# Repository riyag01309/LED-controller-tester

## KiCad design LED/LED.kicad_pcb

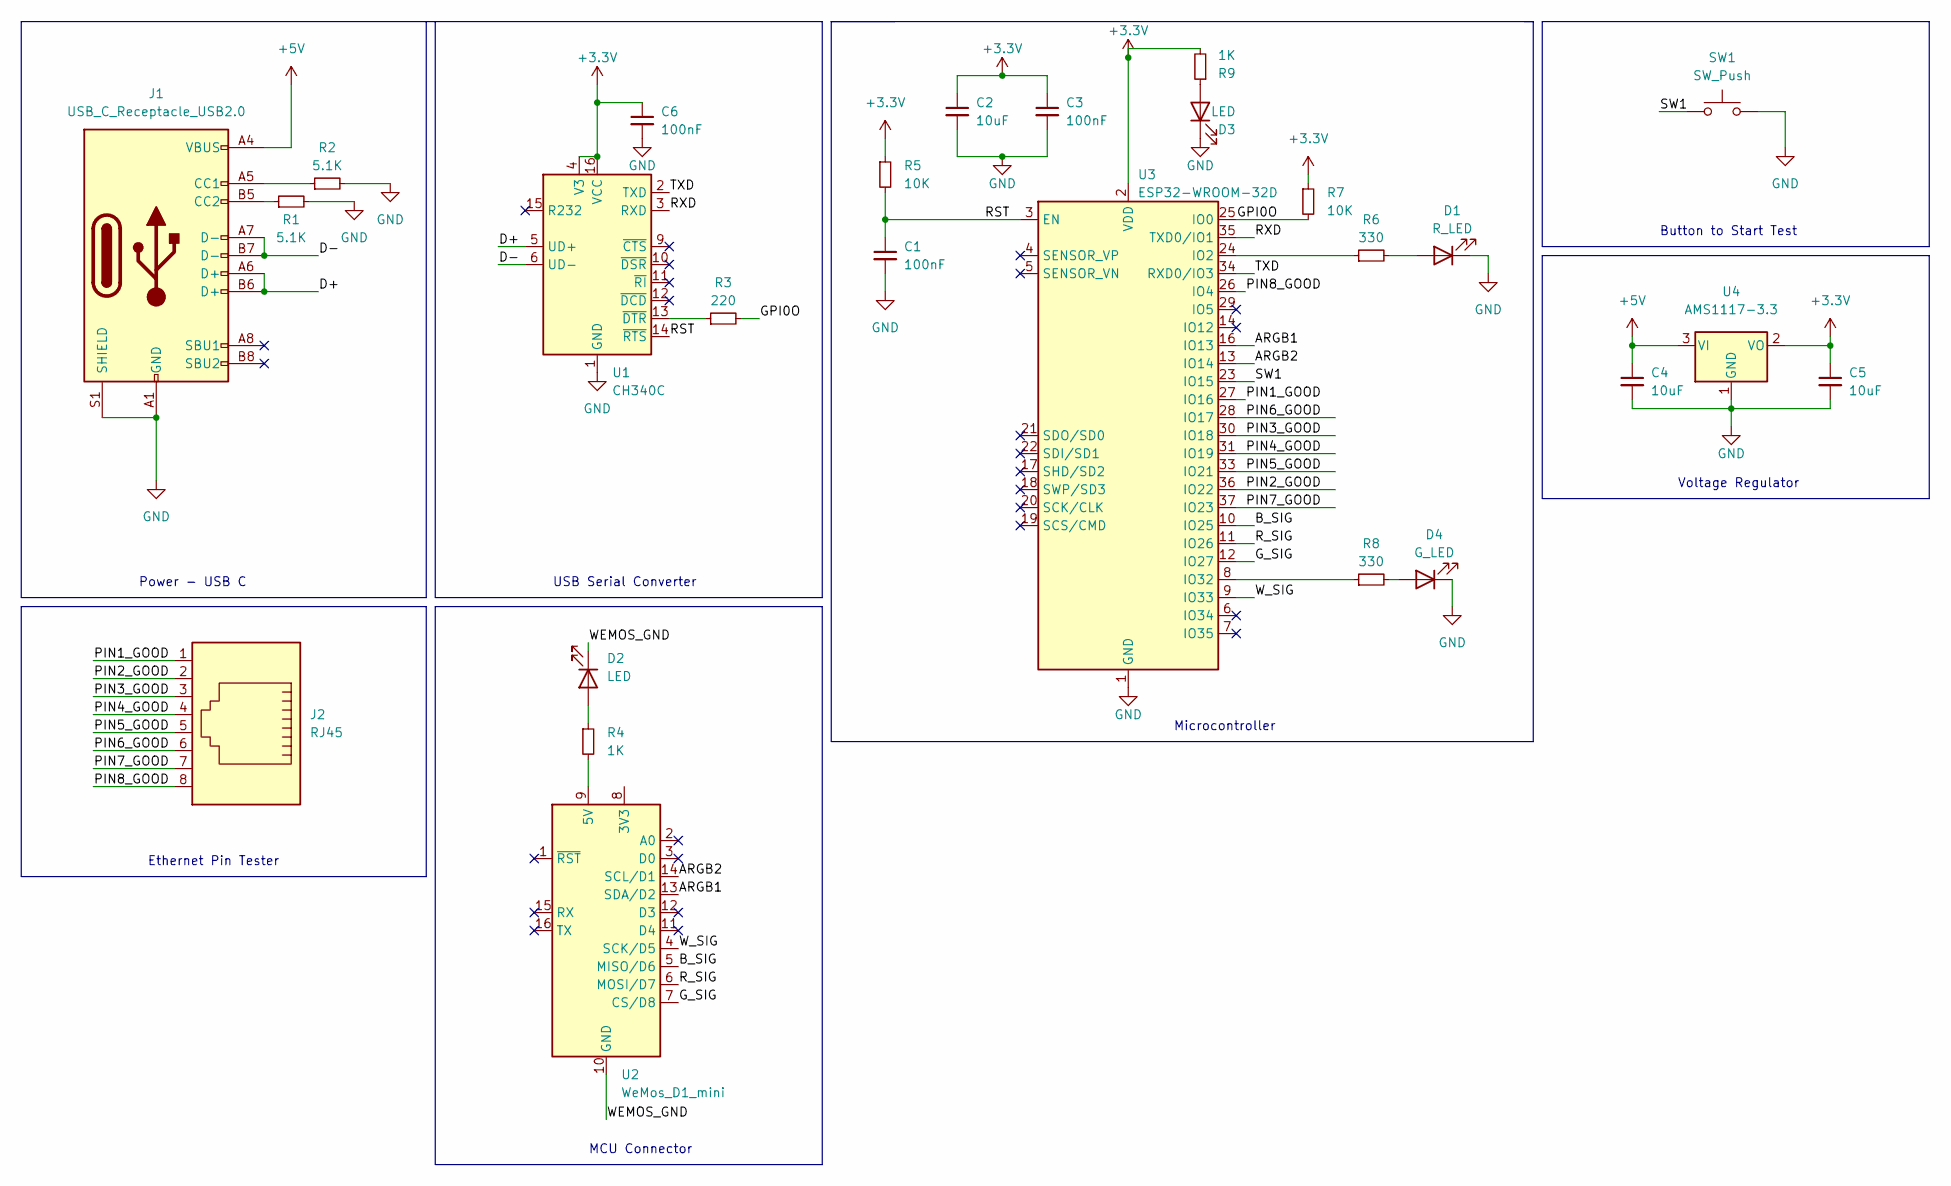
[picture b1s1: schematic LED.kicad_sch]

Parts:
C1, C3, C6: 100nF; C_0402_1005Metric; LCSC C1525
C2, C4, C5: 10uF; C_0603_1608Metric; LCSC C19702
D1: R_LED; LED_0603_1608Metric; LCSC C2286
D2, D3: LED; LED_0603_1608Metric; LCSC C72043
D4: G_LED; LED_0603_1608Metric; LCSC C72043
J1: USB_C_Receptacle_USB2.0; USB_C_Receptacle_Palconn_UTC16-G
J2: RJ45; RJ45_5501-88011111
R1, R2: 5.1K; R_0402_1005Metric; LCSC C25905
R3: 220; R_0402_1005Metric; LCSC C25091
R4, R9: 1K; R_0402_1005Metric; LCSC C11702
R5, R7: 10K; R_0402_1005Metric; LCSC C25744
R6, R8: 330; R_0402_1005Metric; LCSC C25104
SW1: SW_Push; SW_SPST_TL3342; LCSC C318884
U1: CH340C; SOIC-16_3.9x9.9mm_P1.27mm
U2: WeMos_D1_mini; WEMOS_D1_mini_light
U3: ESP32-WROOM-32D; ESP32-WROOM-32
U4: AMS1117-3.3; SOT-223-3_TabPin2; LCSC C6186

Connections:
+3.3V: C2.1, C3.1, C5.1, C6.1, R5.1, R7.1, R9.2, U1.4 (V3), U1.16 (VCC), U3.2 (VDD), U4.2 (VO)
+5V: C4.1, J1.A4 (VBUS), J1.A9 (VBUS), J1.B4 (VBUS), J1.B9 (VBUS), U4.3 (VI)
/ARGB1: U2.13 (SDA/D2), U3.16 (IO13)
/ARGB2: U2.14 (SCL/D1), U3.13 (IO14)
/B_SIG: U2.5 (MISO/D6), U3.10 (IO25)
/D+: J1.A6 (D+), J1.B6 (D+), U1.5 (UD+)
/D-: J1.A7 (D-), J1.B7 (D-), U1.6 (UD-)
/GPI0O: R3.2, R7.2, U3.25 (IO0)
/G_SIG: U2.7 (CS/D8), U3.12 (IO27)
/PIN1_GOOD: J2.1, U3.27 (IO16)
/PIN2_GOOD: J2.2, U3.36 (IO22)
/PIN3_GOOD: J2.3, U3.30 (IO18)
/PIN4_GOOD: J2.4, U3.31 (IO19)
/PIN5_GOOD: J2.5, U3.33 (IO21)
/PIN6_GOOD: J2.6, U3.28 (IO17)
/PIN7_GOOD: J2.7, U3.37 (IO23)
/PIN8_GOOD: J2.8, U3.26 (IO4)
/RST: C1.1, R5.2, U1.14 (~RTS), U3.3 (EN)
/RXD: U1.3 (RXD), U3.35 (TXD0/IO1)
/R_SIG: U2.6 (MOSI/D7), U3.11 (IO26)
/SW1: SW1.1, U3.23 (IO15)
/TXD: U1.2 (TXD), U3.34 (RXD0/IO3)
/WEMOS_GND: D2.1 (K), U2.10 (GND)
/W_SIG: U2.4 (SCK/D5), U3.9 (IO33)
GND: C1.2, C2.2, C3.2, C4.2, C5.2, C6.2, D1.1 (K), D3.1 (K), D4.1 (K), J1.A1 (GND), J1.A12 (GND), J1.B1 (GND), J1.B12 (GND), J1.S1 (SHIELD), R1.2, R2.2, SW1.2, U1.1 (GND), U3.1 (GND), U3.15 (GND), U3.38 (GND), U3.39 (GND), U4.1 (GND)
unnamed: D1.2 (A), R6.2
unnamed: D2.2 (A), R4.1
unnamed: D3.2 (A), R9.1
unnamed: D4.2 (A), R8.2
unnamed: J1.A5 (CC1), R2.1
unnamed: J1.B5 (CC2), R1.1
unnamed: R3.1, U1.13 (~DTR)
unnamed: R4.2, U2.9 (5V)
unnamed: R8.1, U3.8 (IO32)
unnamed: R6.1, U3.24 (IO2)

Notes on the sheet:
Ethernet Pin Tester
Microcontroller
MCU Connector
USB Serial Converter
Button to Start Test
Power - USB C
Voltage Regulator

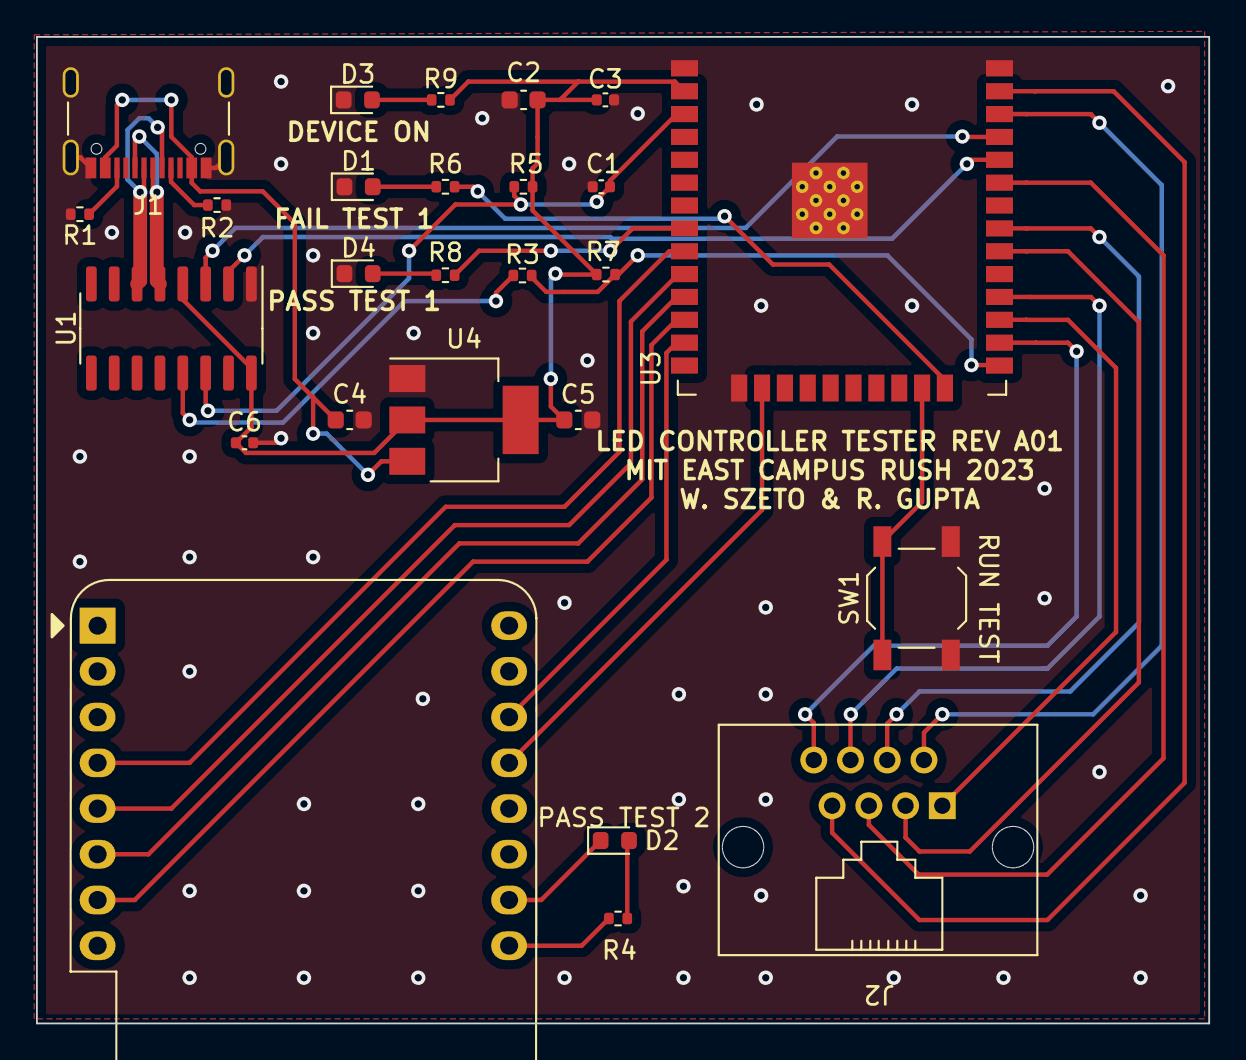
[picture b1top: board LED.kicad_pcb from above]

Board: 2 copper layers, 65.1 x 54.8 mm, 26 parts (0 on the bottom side), 35 nets.

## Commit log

2023-02-03 initial design
2023-02-12 2 ethernet
2023-02-12 2/12
    first draft
2023-02-12 to gnd
2023-02-12 less errors
2023-02-12 even less errors
2023-02-12 labelled
2023-02-16 Routing Done
2023-02-20 2/20
2023-02-20 small updates
2023-02-26 Final PCB Version 1
2023-03-28 Final Board
